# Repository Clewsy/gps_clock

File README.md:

gps_clock has the following features and characteristics:
- 16 digit 7-segment LED display.
- Date/Time display [EPOCH][link_web_wikipedia_epoch_time] format (seconds elapsed since 1970-01-01).
- Date/Time display [ISO-8601][link_web_wikipedia_iso-8601] format (YYYY.MM.DD.HH.MM.SS).
- Adjustable brightness (setting retained with power-cycle).
- Programmable UTC offset from -12hrs to +12hrs in half-hour increments to match any timezone (setting retained with power-cycle).
- RTC with battery back-up to retain time with power-cycle and/or absence of GPS signal.

The [code][link_repo_code], schematics ([control board][link_repo_schematic_control] & [display board][link_repo_schematic_display]) and PCB layouts ([control board][link_repo_pcb_control] & [display board][link_repo_pcb_display]) are all included here on gitlab.

Additional info and photos can be found [here][link_clews_projects_gps_clock].

Proudly mentioned at [hackaday.com][link_web_hackaday_gpsclock] (and linked again in a [later article][link_web_hackaday_iso8601]).

![The completed gps_clock.][image_gps_clock]

[link_web_wikipedia_epoch_time]:https://en.wikipedia.org/wiki/Epoch_time
[link_web_wikipedia_iso-8601]:https://en.wikipedia.org/wiki/ISO-8601
[link_web_hackaday_gpsclock]:https://hackaday.com/2018/09/18/epic-clock-clocks-the-unix-epoch/
[link_web_hackaday_iso8601]:https://hackaday.com/2021/04/21/iso-8601-ending-the-date-wars-and-confusing-everyone-equally/
[link_repo_code]:code/
[link_repo_schematic_control]:pcb/schematic_gps_clock_control_board.pdf
[link_repo_schematic_display]:pcb/schematic_gps_clock_display_board.pdf
[link_repo_pcb_display]:pcb/cl0ck_control/
[link_repo_pcb_control]:pcb/cl0ck_display/

[link_clews_projects_gps_clock]:https://clews.pro/projects/gps_clock.php

[image_gps_clock]:images/gps_clock_github_photo.jpg

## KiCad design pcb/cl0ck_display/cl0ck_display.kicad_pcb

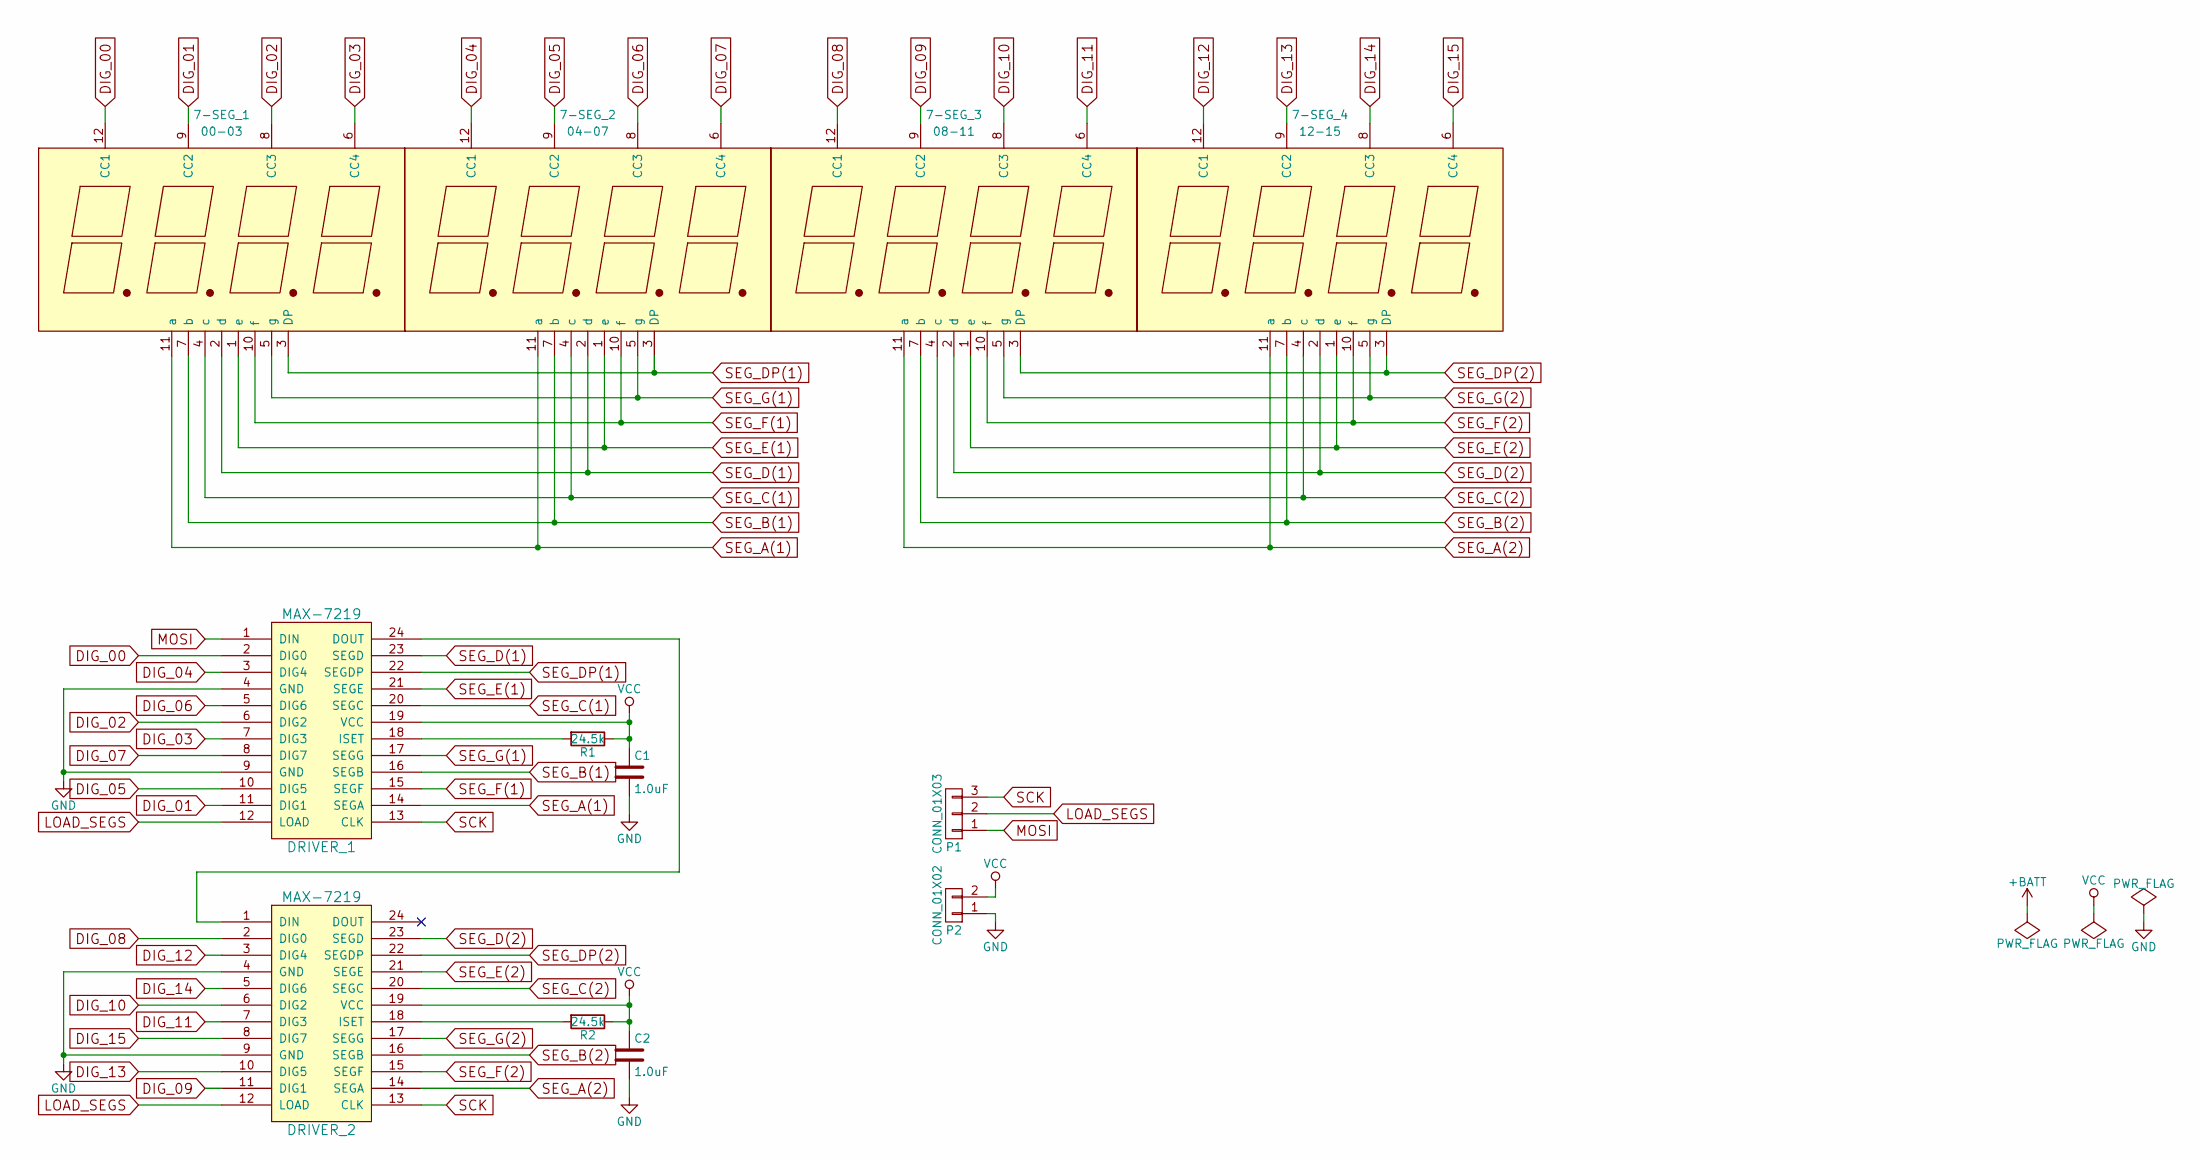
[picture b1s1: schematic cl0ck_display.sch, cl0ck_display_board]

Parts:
7-SEG_1: 00-03; 4x7-SEG
7-SEG_2: 04-07; 4x7-SEG
7-SEG_3: 08-11; 4x7-SEG
7-SEG_4: 12-15; 4x7-SEG
C1, C2: 1.0uF; C_0603
DRIVER_1, DRIVER_2: MAX-7219; SOIC-24W_7.5x15.4mm_Pitch1.27mm
P1: CONN_01X03; Pin_Header_Straight_1x03
P2: CONN_01X02; Pin_Header_Straight_1x02
R1, R2: 24.5k; R_0603

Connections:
DIG_00: 7-SEG_1.12 (CC1), DRIVER_1.2 (DIG0)
DIG_01: 7-SEG_1.9 (CC2), DRIVER_1.11 (DIG1)
DIG_02: 7-SEG_1.8 (CC3), DRIVER_1.6 (DIG2)
DIG_03: 7-SEG_1.6 (CC4), DRIVER_1.7 (DIG3)
DIG_04: 7-SEG_2.12 (CC1), DRIVER_1.3 (DIG4)
DIG_05: 7-SEG_2.9 (CC2), DRIVER_1.10 (DIG5)
DIG_06: 7-SEG_2.8 (CC3), DRIVER_1.5 (DIG6)
DIG_07: 7-SEG_2.6 (CC4), DRIVER_1.8 (DIG7)
DIG_08: 7-SEG_3.12 (CC1), DRIVER_2.2 (DIG0)
DIG_09: 7-SEG_3.9 (CC2), DRIVER_2.11 (DIG1)
DIG_10: 7-SEG_3.8 (CC3), DRIVER_2.6 (DIG2)
DIG_11: 7-SEG_3.6 (CC4), DRIVER_2.7 (DIG3)
DIG_12: 7-SEG_4.12 (CC1), DRIVER_2.3 (DIG4)
DIG_13: 7-SEG_4.9 (CC2), DRIVER_2.10 (DIG5)
DIG_14: 7-SEG_4.8 (CC3), DRIVER_2.5 (DIG6)
DIG_15: 7-SEG_4.6 (CC4), DRIVER_2.8 (DIG7)
GND: C1.2, C2.2, DRIVER_1.4 (GND), DRIVER_1.9 (GND), DRIVER_2.4 (GND), DRIVER_2.9 (GND), P2.1
LOAD_SEGS: DRIVER_1.12 (LOAD), DRIVER_2.12 (LOAD), P1.2
MOSI: DRIVER_1.1 (DIN), P1.1
unnamed: DRIVER_1.18 (ISET), R1.2
unnamed: DRIVER_1.24 (DOUT), DRIVER_2.1 (DIN)
unnamed: DRIVER_2.18 (ISET), R2.2
SCK: DRIVER_1.13 (CLK), DRIVER_2.13 (CLK), P1.3
SEG_A(1): 7-SEG_1.11 (a), 7-SEG_2.11 (a), DRIVER_1.14 (SEGA)
SEG_A(2): 7-SEG_3.11 (a), 7-SEG_4.11 (a), DRIVER_2.14 (SEGA)
SEG_B(1): 7-SEG_1.7 (b), 7-SEG_2.7 (b), DRIVER_1.16 (SEGB)
SEG_B(2): 7-SEG_3.7 (b), 7-SEG_4.7 (b), DRIVER_2.16 (SEGB)
SEG_C(1): 7-SEG_1.4 (c), 7-SEG_2.4 (c), DRIVER_1.20 (SEGC)
SEG_C(2): 7-SEG_3.4 (c), 7-SEG_4.4 (c), DRIVER_2.20 (SEGC)
SEG_D(1): 7-SEG_1.2 (d), 7-SEG_2.2 (d), DRIVER_1.23 (SEGD)
SEG_D(2): 7-SEG_3.2 (d), 7-SEG_4.2 (d), DRIVER_2.23 (SEGD)
SEG_DP(1): 7-SEG_1.3 (DP), 7-SEG_2.3 (DP), DRIVER_1.22 (SEGDP)
SEG_DP(2): 7-SEG_3.3 (DP), 7-SEG_4.3 (DP), DRIVER_2.22 (SEGDP)
SEG_E(1): 7-SEG_1.1 (e), 7-SEG_2.1 (e), DRIVER_1.21 (SEGE)
SEG_E(2): 7-SEG_3.1 (e), 7-SEG_4.1 (e), DRIVER_2.21 (SEGE)
SEG_F(1): 7-SEG_1.10 (f), 7-SEG_2.10 (f), DRIVER_1.15 (SEGF)
SEG_F(2): 7-SEG_3.10 (f), 7-SEG_4.10 (f), DRIVER_2.15 (SEGF)
SEG_G(1): 7-SEG_1.5 (g), 7-SEG_2.5 (g), DRIVER_1.17 (SEGG)
SEG_G(2): 7-SEG_3.5 (g), 7-SEG_4.5 (g), DRIVER_2.17 (SEGG)
VCC: C1.1, C2.1, DRIVER_1.19 (VCC), DRIVER_2.19 (VCC), P2.2, R1.1, R2.1

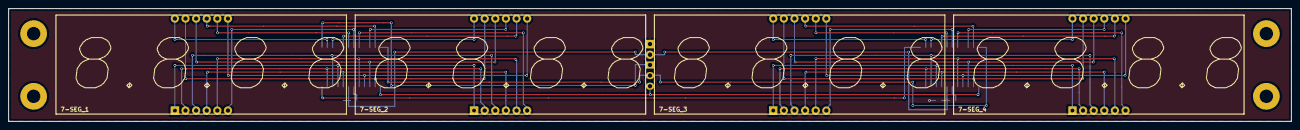
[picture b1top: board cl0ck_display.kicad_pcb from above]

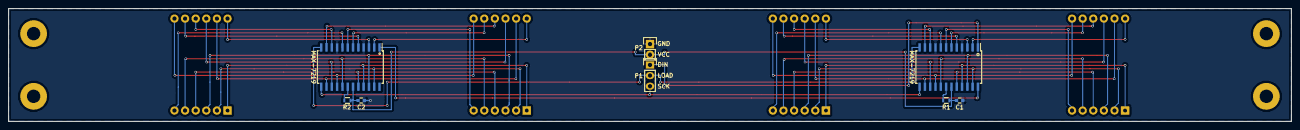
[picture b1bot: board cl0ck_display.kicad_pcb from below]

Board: 2 copper layers, 307.0 x 27.0 mm, 12 parts (8 on the bottom side), 40 nets.

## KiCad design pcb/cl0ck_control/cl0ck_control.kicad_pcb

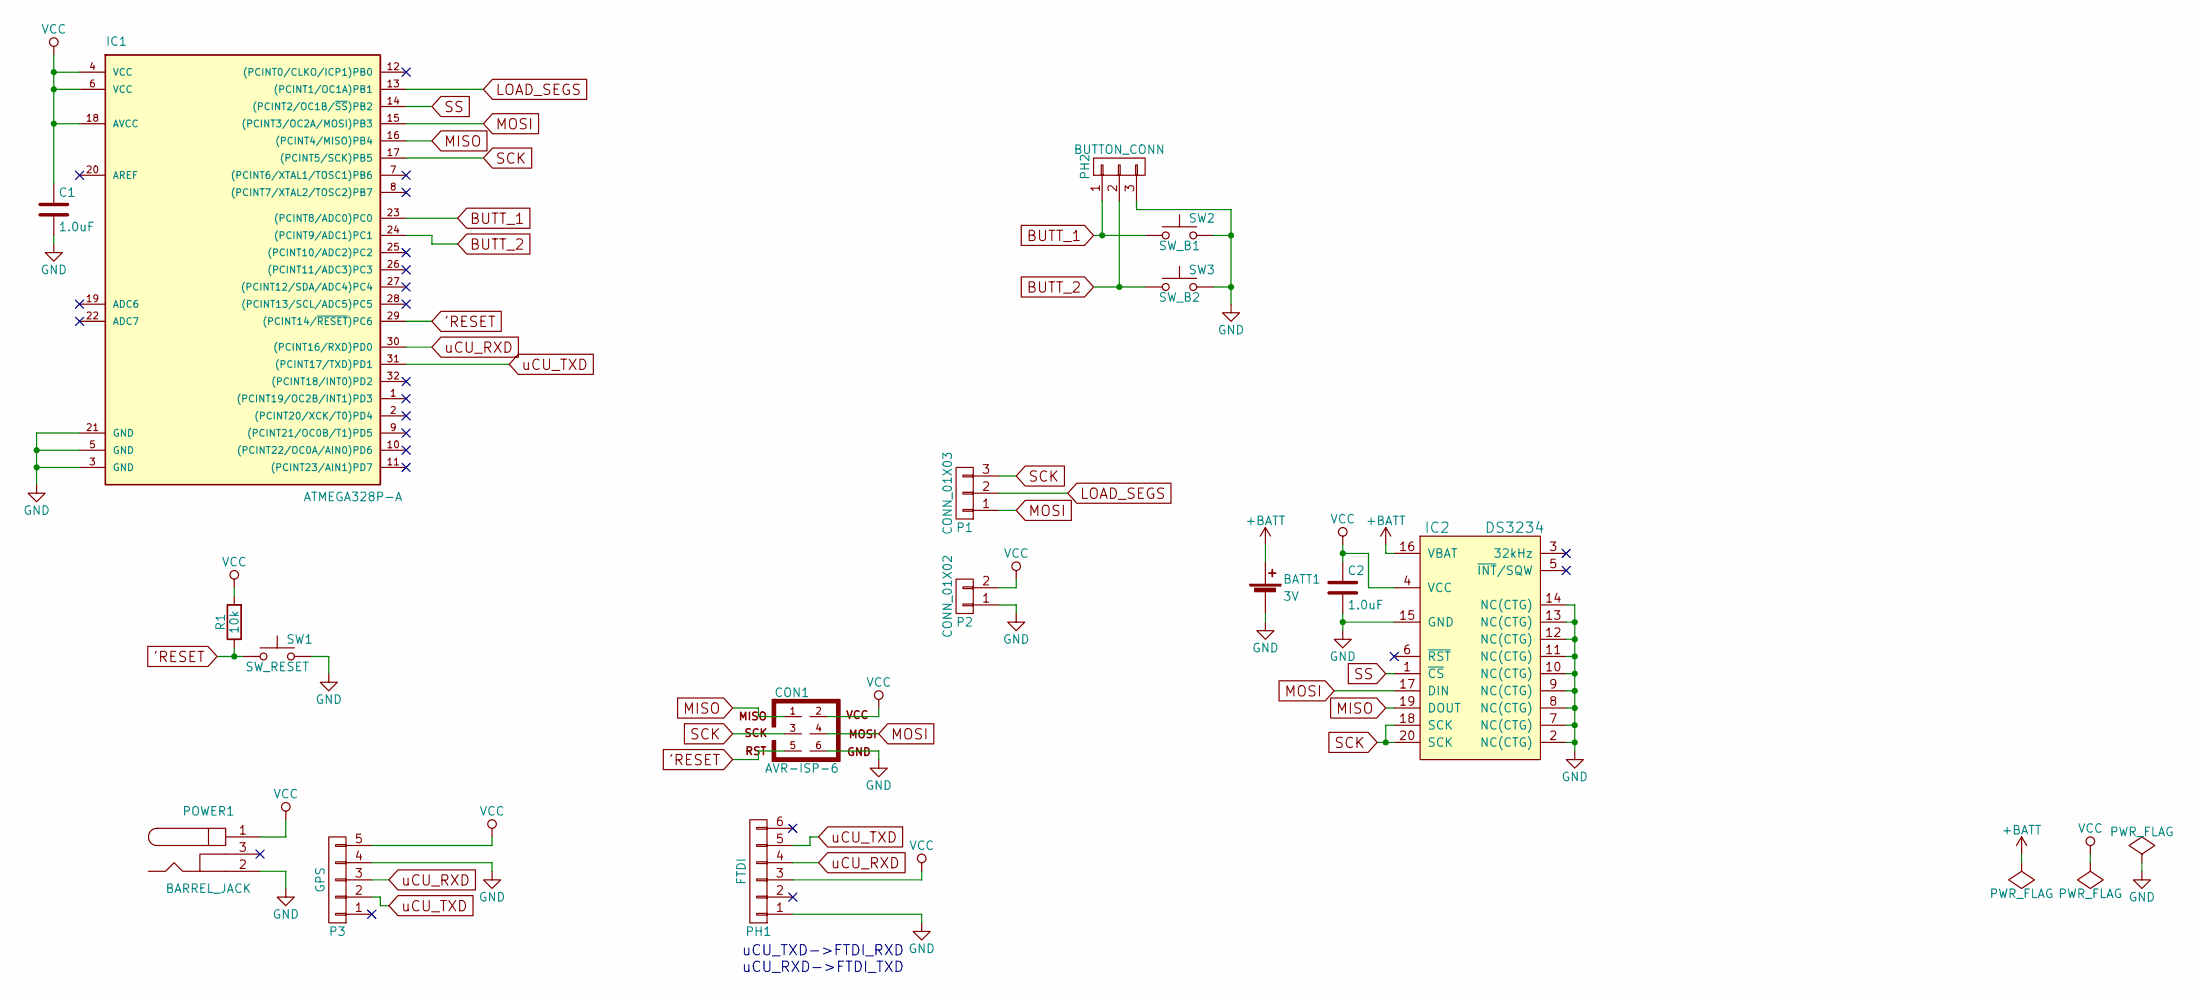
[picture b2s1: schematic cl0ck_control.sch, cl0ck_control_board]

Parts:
BATT1: 3V; Keystone_3000_1x12mm-CoinCell
C1, C2: 1.0uF; C_0603
CON1: AVR-ISP-6; Pin_Header_Straight_2x03
IC1: ATMEGA328P-A; TQFP-32_7x7mm_Pitch0.8mm
IC2: DS3234; SOIC-20W_7.5x12.8mm_Pitch1.27mm
P1: CONN_01X03; Pin_Header_Angled_1x03
P2: CONN_01X02; Pin_Header_Angled_1x02
P3: GPS; Pin_Header_Angled_1x05
PH1: FTDI; Pin_Header_Angled_1x06
PH2: BUTTON_CONN; Pin_Header_Angled_1x03
POWER1: BARREL_JACK
R1: 10k; R_0603
SW1: SW_RESET; SW_SPST_PTS645
SW2: SW_B1; SW_SPST_PTS645
SW3: SW_B2; SW_SPST_PTS645

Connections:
'RESET: CON1.5, IC1.29 ((PCINT14/~RESET~)PC6), R1.1, SW1.1
+BATT: BATT1.1 (+), IC2.16 (VBAT)
BUTT_1: IC1.23 ((PCINT8/ADC0)PC0), PH2.1, SW2.1
BUTT_2: IC1.24 ((PCINT9/ADC1)PC1), PH2.2, SW3.1
GND: BATT1.2 (-), C1.2, C2.2, CON1.6, IC1.3 (GND), IC1.5 (GND), IC1.21 (GND), IC2.2 (NC(CTG)), IC2.7 (NC(CTG)), IC2.8 (NC(CTG)), IC2.9 (NC(CTG)), IC2.10 (NC(CTG)), IC2.11 (NC(CTG)), IC2.12 (NC(CTG)), IC2.13 (NC(CTG)), IC2.14 (NC(CTG)), IC2.15 (GND), P2.1, P3.4, PH1.1, PH2.3, POWER1.2, SW1.2, SW2.2, SW3.2
LOAD_SEGS: IC1.13 ((PCINT1/OC1A)PB1), P1.2
MISO: CON1.1, IC1.16 ((PCINT4/MISO)PB4), IC2.19 (DOUT)
MOSI: CON1.4, IC1.15 ((PCINT3/OC2A/MOSI)PB3), IC2.17 (DIN), P1.1
SCK: CON1.3, IC1.17 ((PCINT5/SCK)PB5), IC2.18 (SCK), IC2.20 (SCK), P1.3
SS: IC1.14 ((PCINT2/OC1B/~SS~)PB2), IC2.1 (~CS~)
VCC: C1.1, C2.1, CON1.2, IC1.4 (VCC), IC1.6 (VCC), IC1.18 (AVCC), IC2.4 (VCC), P2.2, P3.5, PH1.3, POWER1.1, R1.2
uCU_RXD: IC1.30 ((PCINT16/RXD)PD0), P3.3, PH1.4
uCU_TXD: IC1.31 ((PCINT17/TXD)PD1), P3.2, PH1.5

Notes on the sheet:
uCU_TXD->FTDI_RXD uCU_RXD->FTDI_TXD

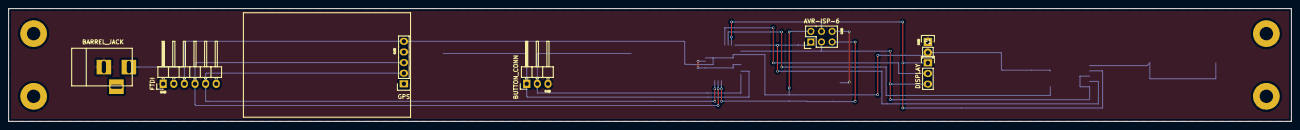
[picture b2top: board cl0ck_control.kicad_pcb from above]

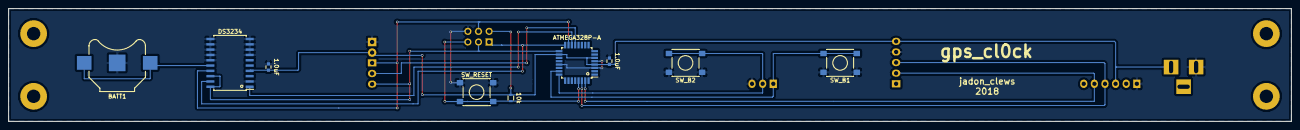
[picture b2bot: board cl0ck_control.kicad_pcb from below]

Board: 2 copper layers, 307.0 x 27.0 mm, 16 parts (9 on the bottom side), 13 nets.

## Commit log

2018-06-18 Began iteration to rev_1.
2018-06-18 Split schematic into two separate boards.
2018-06-18 Added library file for custom components.
2018-06-18 Created display PCB from schematic.
2018-06-18 Working on control pcb.
2018-06-19 Revision to control pcb.
2018-06-19 Revision to pcbs.
2018-07-25 Prototype display board PCB fabricated. One error found - decoupling capacitor not grounded. Iterated pcb layout to remedy (added via).
2018-07-25 Display circuit board assembled and functioning. Begun reworking the code. Implemented USART, SPI and MAX7219 driver.
2018-07-26 Added basic UTC time parse from GPS module and output to 7-seg display
2018-07-29 Cleaned code, added comments, implemented display buffer and display modes.
2018-07-30 Revised control schematic and PCB files. Finalised and ordered first trial run.
2018-08-07 Added some error-checking when syncing time from gps. Also other tweaks.
2018-08-23 Control PCB assembled and working. Coded implementation of RTC (ds3234) comms.
2018-08-24 Implemented pin-change interrupt triggered by button press (can now cycle through display modes by button).
2018-08-24 Fixed loop when pressing mode button.
2018-09-03 Implemented a function for printing psuedo 'text' to the display (e.g. 'SynCIng'
2018-09-04 Implemented EPOCH TIME!
2018-09-05 Implemented sync button to initiate an attempt at syncing time to GPS. Fixed errors in PCint vector.
2018-09-05 Can set a UTC offset hours value. Offset currently has no effect on time and is not retained with power-cycle (TBD).
2018-09-05 Added comments and broke up some functions for readability.
2018-09-06 Implemented timexone adjustment (UTC offset) including epprom save.
2018-09-07 Added a fifth mode to allow setting display intensity (brightness). Currently has no effect (TBD)
2018-09-08 Implemented intensity (brightness) control. Code readability improvements.
2018-09-08 Improved function sev_seg_set_word.
2018-09-15 Tidied schematics and generated pdfs.
2018-09-18 Create LICENSE
2018-09-18 Added README.
2018-09-18 Added photo to README.
2018-09-21 Updated readme.
2018-09-22 Tweaked the PCINT ISR and de-bounce value to work better with these mushy buttons.
2018-09-22 More tweaking of the PCINT ISR to improve mode transitions.
2018-09-22 Added some comments.
2018-10-19 Fixed an error in date rollover when adjusting for UTC offset.
2019-09-14 Tweaked PCB before second time ordering fab.
2020-04-09 Readme overhaul.
2020-04-09 Restructured repo.
2020-04-09 Compressed rev0.
2020-04-21 Added link.
2020-04-21 Typo.
2021-04-26 Added link to iso8601 article.
